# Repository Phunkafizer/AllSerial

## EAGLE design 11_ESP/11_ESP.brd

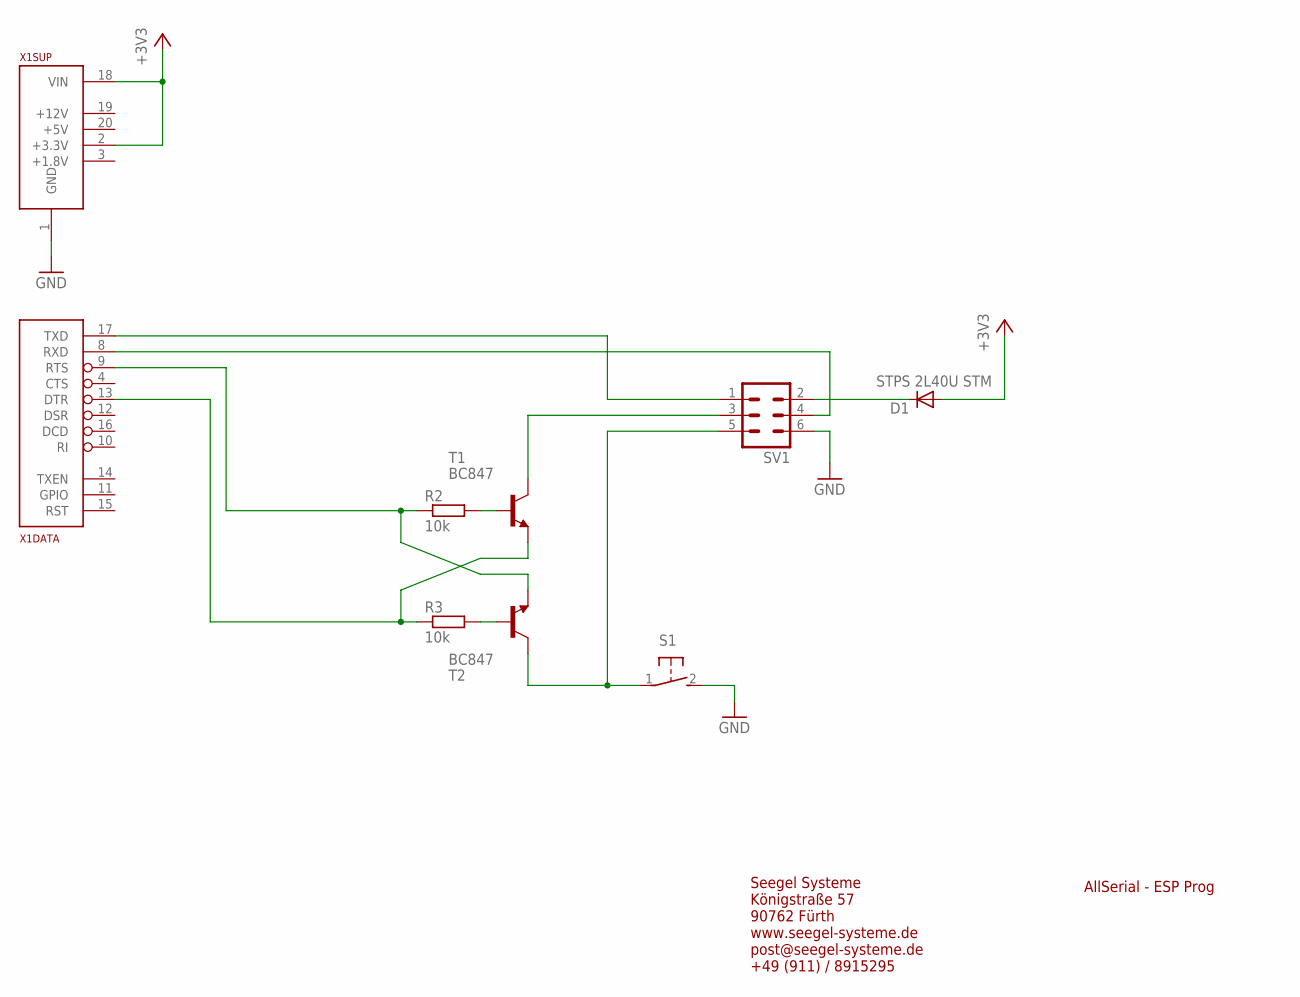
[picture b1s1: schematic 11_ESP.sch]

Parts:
D1: STPS 2L40U STM; DO214AA
R2, R3: 10k; R0805
S1: 31-XX; B3F-31XX
SV1: ML6L
T1, T2: BC847; SOT23
X1: ALLSERIALSLAVE; DAUGHTER-THT

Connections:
+3V3: D1.A, X1.2 (+3.3V), X1.18 (VIN)
GND: S1.2 (S), SV1.6, X1.1 (GND)
unnamed: D1.C, SV1.2
unnamed: R3.1, T1.2 (E), X1.13 (DTR)
unnamed: SV1.3, T1.3 (C)
unnamed: S1.1, SV1.5, T2.3 (C)
unnamed: R2.1, T2.2 (E), X1.9 (RTS)
unnamed: SV1.1, X1.17 (TXD)
unnamed: R2.2, T1.1 (B)
unnamed: R3.2, T2.1 (B)
unnamed: SV1.4, X1.8 (RXD)

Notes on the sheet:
AllSerial - ESP Prog
Seegel Systeme Königstraße 57 90762 Fürth www.seegel-systeme.de post@seegel-systeme.de +49 (911) / 8915295

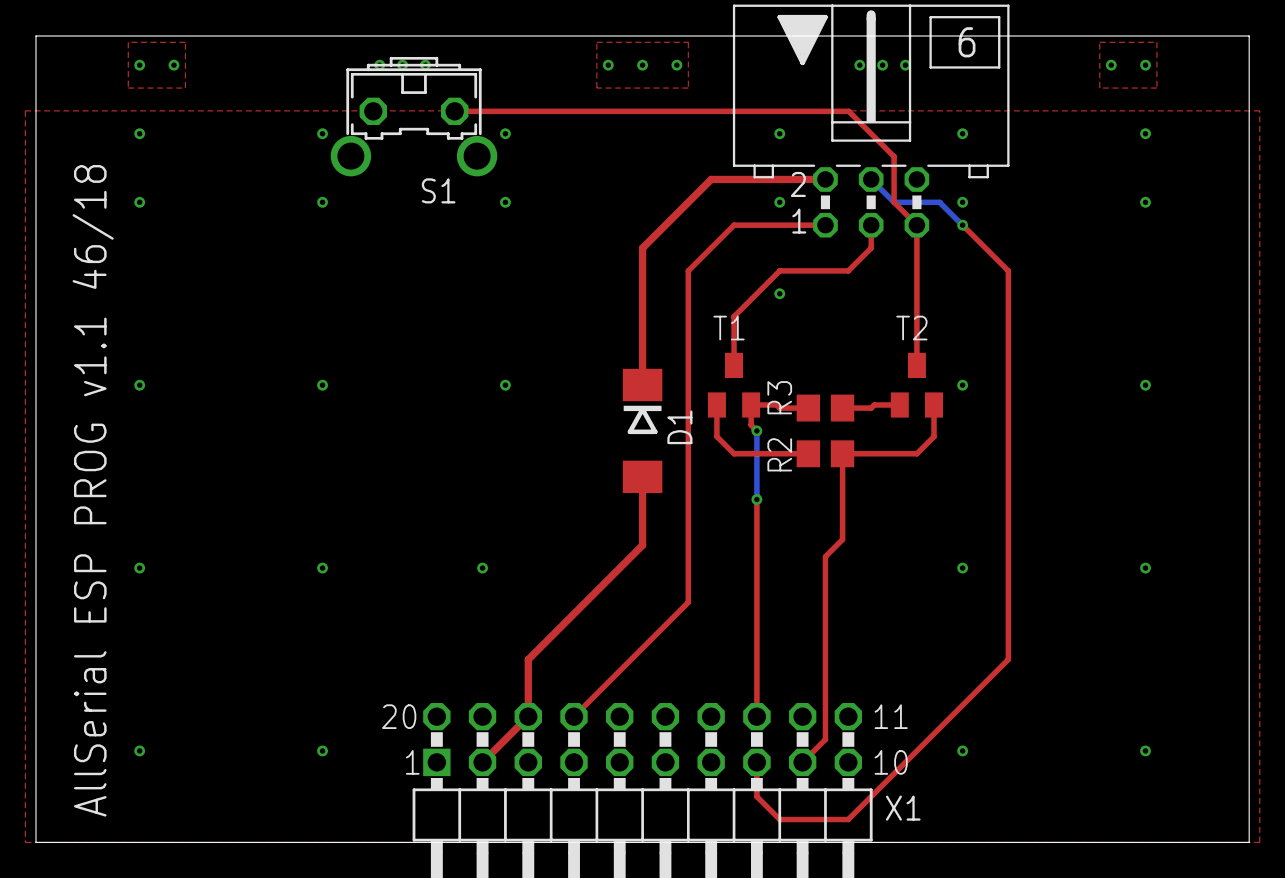
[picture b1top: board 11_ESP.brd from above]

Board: 2 copper layers, 67.4 x 44.8 mm, 8 parts (0 on the bottom side), 11 nets.

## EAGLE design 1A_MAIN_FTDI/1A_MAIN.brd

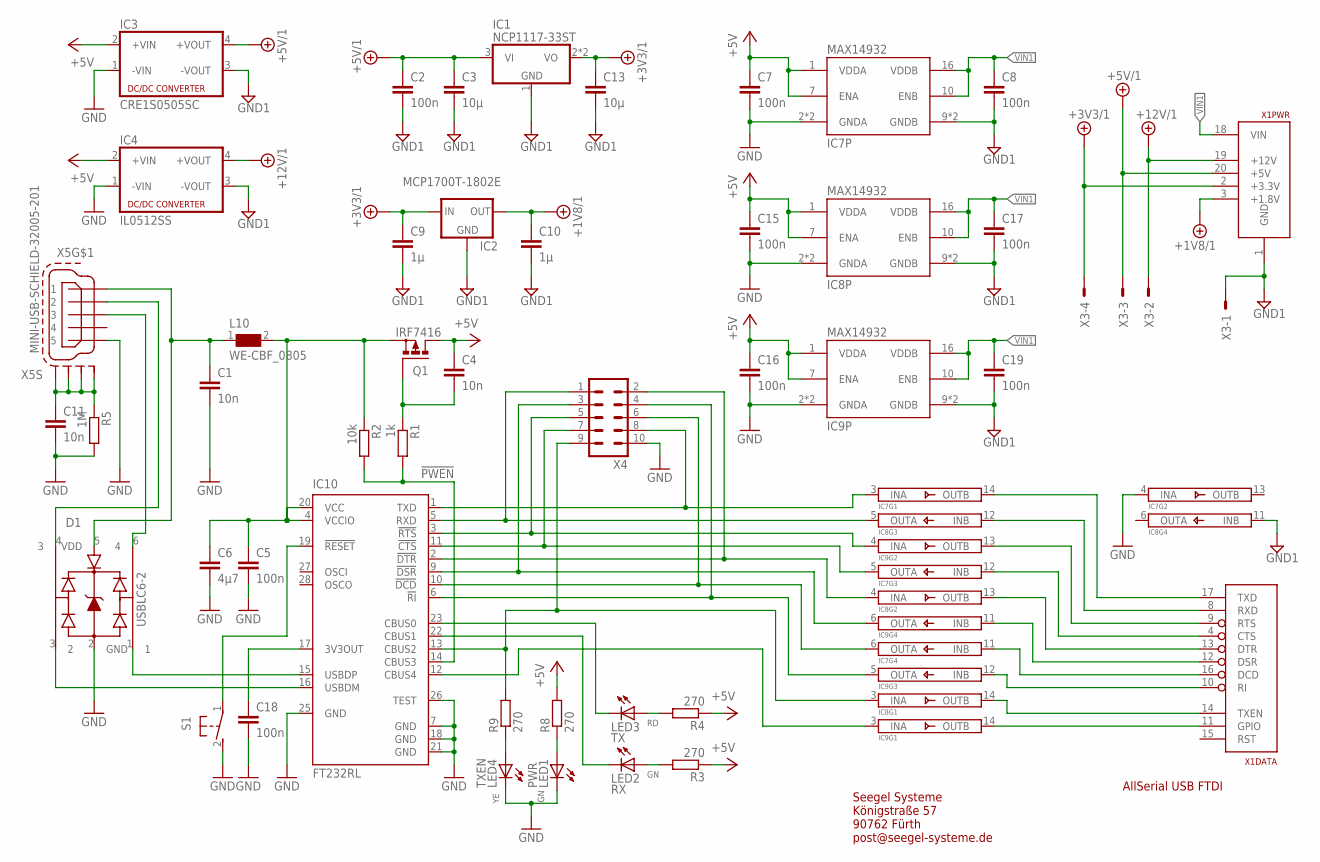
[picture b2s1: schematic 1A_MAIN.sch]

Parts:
C1, C4, C11: 10n; C0805
C2, C5, C7, C8, C15, C16, C17, C18, C19: 100n; C0805
C3, C13: 10µ; C0805
C6: 4µ7; C0805
C9, C10: 1µ; C0805
D1: USBLC6-2; WE-TVS_SOT23-6L
IC1: NCP1117-33ST; SOT223
IC2: MCP1700T-1802E; SOT23
IC3: CRE1S0505SC; MURATA-SC
IC4: IL0512SS; XPPOWER-SIP
IC7, IC8, IC9: MAX14932; SO16
IC10: FT232RL; SSOP28
L10: WE-CBF_0805; 0805
LED1: PWR; CHIPLED_0603
LED2: RX; CHIPLED_0603
LED3: TX; CHIPLED_0603
LED4: TXEN; CHIPLED_0603
Q1: IRF7416; SO-08
R1: 1k; R0805
R2: 10k; R0805
R3, R4, R8, R9: 270; R0805
R5: 1M; R0805
S1: 31-XX; B3F-31XX
X1: ALLSERIALMASTERMM; MAIN-THT
X3: AKL18X-04W; AKL182-04
X4: ML10
X5: MINI-USB-SCHIELD-32005-201; 32005-201

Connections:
!PWEN: IC10.14 (CBUS3), R1.2, R2.2
+1V8/1: C10.1, IC2.2 (OUT), X1.3 (+1.8V)
+3V3/1: C9.1, C13.1, IC1.2 (VO), IC1.4 (VO), IC2.3 (IN), X1.2 (+3.3V), X3.P$4
+5V: C4.1, C7.1, C15.1, C16.1, IC3.2 (+VIN), IC4.2 (+VIN), IC7.1 (VDDA), IC7.7 (ENA), IC8.1 (VDDA), IC8.7 (ENA), IC9.1 (VDDA), IC9.7 (ENA), Q1.5 (D), Q1.6 (D), Q1.7 (D), Q1.8 (D), R3.1, R4.1, R8.2
+5V/1: C2.1, C3.1, IC1.3 (VI), IC3.4 (+VOUT), X1.20 (+5V), X3.P$3
+12V/1: IC4.4 (+VOUT), X1.19 (+12V), X3.P$2
GND: C1.2, C5.2, C6.2, C7.2, C11.2, C15.2, C16.2, C18.2, D1.2 (GND), IC3.1 (-VIN), IC4.1 (-VIN), IC7.2 (GNDA), IC7.4 (INA), IC7.8 (GNDA), IC8.2 (GNDA), IC8.8 (GNDA), IC9.2 (GNDA), IC9.8 (GNDA), IC10.7 (GND), IC10.18 (GND), IC10.21 (GND), IC10.25 (GND), IC10.26 (TEST), LED1.C, LED4.C, R5.2, S1.2 (S), X4.10, X5.5
GND1: C2.2, C3.2, C8.2, C9.2, C10.2, C13.2, C17.2, C19.2, IC1.1 (GND), IC2.1 (GND), IC3.3 (-VOUT), IC4.3 (-VOUT), IC7.9 (GNDB), IC7.15 (GNDB), IC8.9 (GNDB), IC8.11 (INB), IC8.15 (GNDB), IC9.9 (GNDB), IC9.15 (GNDB), X1.1 (GND), X3.P$1
unnamed: IC8.5 (OUTA), IC10.5 (RXD), X4.1
unnamed: IC9.6 (OUTA), IC10.9 (!DSR), X4.3
unnamed: IC8.3 (INA), IC10.13 (CBUS2), R9.2, X4.9
unnamed: LED2.A, R3.2
unnamed: IC10.19 (!RESET), S1.1
unnamed: LED3.A, R4.2
unnamed: LED4.A, R9.1
unnamed: LED1.A, R8.1
unnamed: D1.3 (2), IC10.16 (USBDM)
unnamed: D1.1, IC10.15 (USBDP)
unnamed: C1.1, D1.5 (VDD), L10.1, X5.1
unnamed: D1.4 (3), X5.2
unnamed: IC9.3 (INA), IC10.12 (CBUS4)
unnamed: IC7.3 (INA), IC10.1 (TXD), X4.8
unnamed: D1.6 (4), X5.3
unnamed: C11.1, R5.1, X5.M1 (S1), X5.M2 (S2), X5.M3 (S3), X5.M4 (S4)
unnamed: C18.1, IC10.17 (3V3OUT)
unnamed: IC9.4 (INA), IC10.3 (!RTS), X4.5
unnamed: IC7.5 (OUTA), IC10.11 (!CTS), X4.7
unnamed: IC8.4 (INA), IC10.2 (!DTR), X4.2
unnamed: IC7.6 (OUTA), IC10.10 (!DCD), X4.6
unnamed: IC9.5 (OUTA), IC10.6 (!RI), X4.4
unnamed: C5.1, C6.1, IC10.4 (VCCIO), IC10.20 (VCC), L10.2, Q1.1 (S), Q1.2 (S), Q1.3 (S), R2.1
unnamed: C4.2, Q1.4 (G), R1.1
unnamed: IC7.14 (OUTB), X1.17 (TXD)
unnamed: IC8.12 (INB), X1.8 (RXD)
unnamed: IC9.13 (OUTB), X1.9 (RTS)
unnamed: IC7.12 (INB), X1.4 (CTS)
unnamed: IC8.13 (OUTB), X1.13 (DTR)
unnamed: IC9.11 (INB), X1.12 (DSR)
unnamed: IC7.11 (INB), X1.16 (DCD)
unnamed: IC9.12 (INB), X1.10 (RI)
unnamed: IC8.14 (OUTB), X1.14 (TXEN)
unnamed: IC9.14 (OUTB), X1.11 (GPIO)
RXLED: IC10.22 (CBUS1), LED2.C
TXLED: IC10.23 (CBUS0), LED3.C
VIN1: C8.1, C17.1, C19.1, IC7.10 (ENB), IC7.16 (VDDB), IC8.10 (ENB), IC8.16 (VDDB), IC9.10 (ENB), IC9.16 (VDDB), X1.18 (VIN)

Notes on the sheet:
AllSerial USB FTDI
Seegel Systeme Königstraße 57 90762 Fürth post@seegel-systeme.de

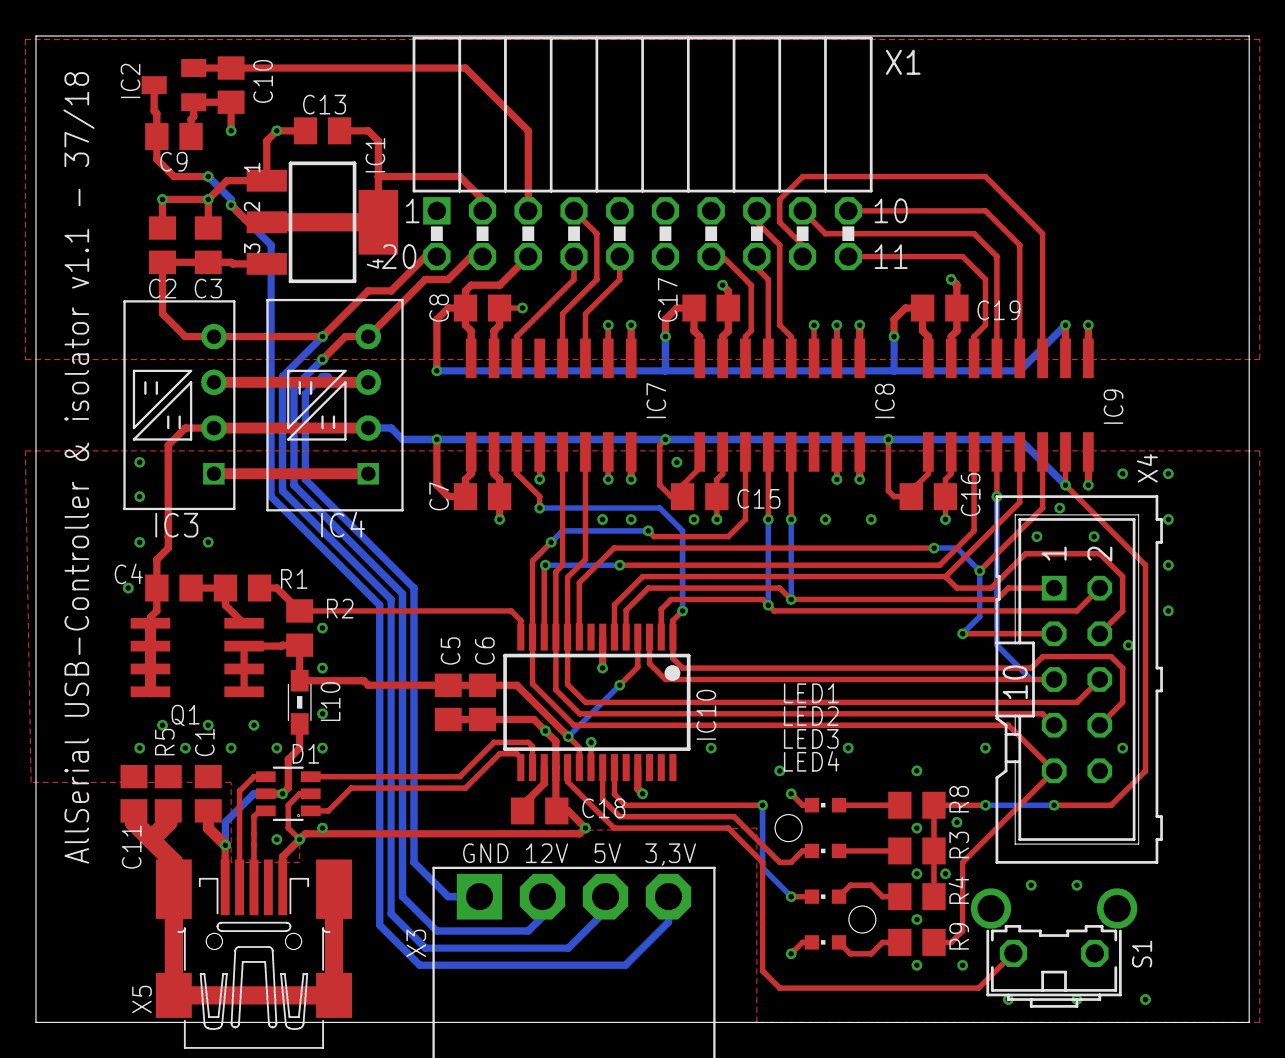
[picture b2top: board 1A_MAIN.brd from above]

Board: 2 copper layers, 67.4 x 54.8 mm, 45 parts (0 on the bottom side), 45 nets.

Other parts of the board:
U$3: 1296.1004

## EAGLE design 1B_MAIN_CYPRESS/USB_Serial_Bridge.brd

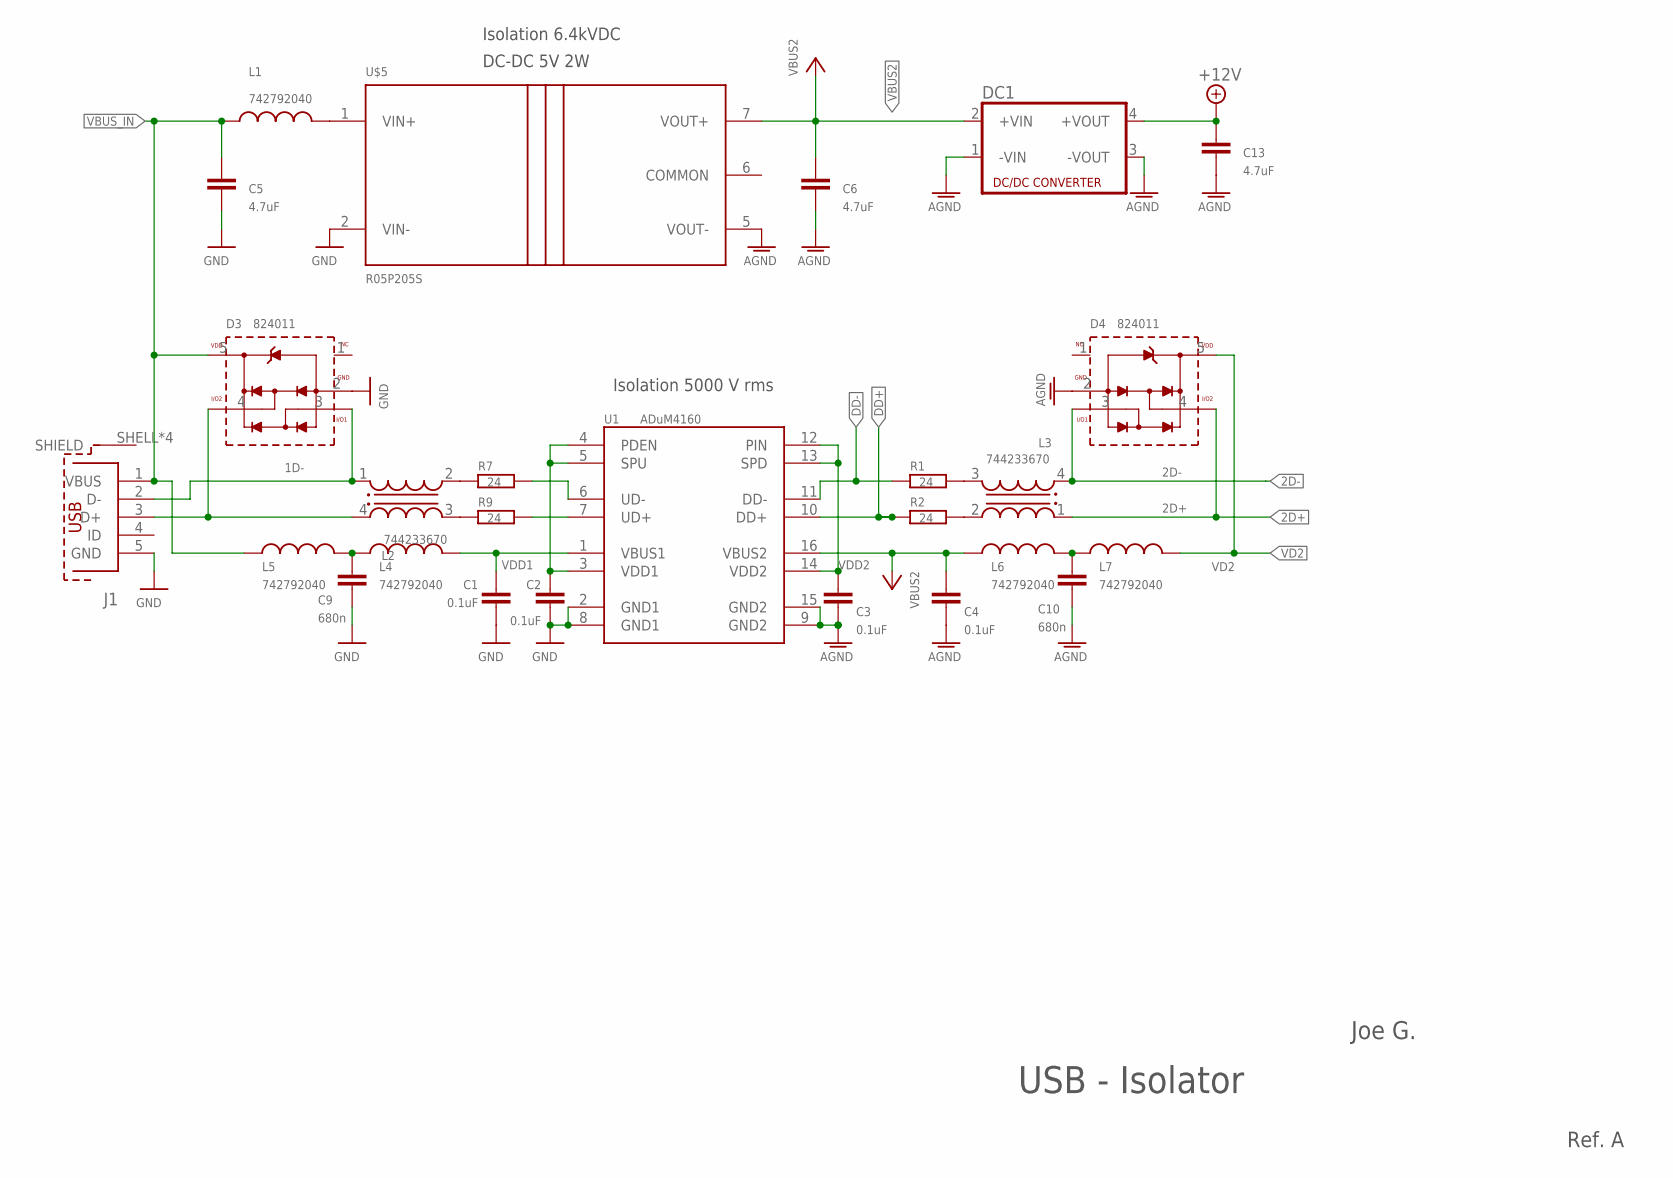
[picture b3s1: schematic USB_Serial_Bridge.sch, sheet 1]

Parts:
C1, C2, C3, C4: 0.1uF; 0805
C5, C6, C13: 4.7uF; 1206
C9: 680n; C0805K
C10: 680n; C0805
D3, D4: 824011; WE-TVS_SOT23-5L
DC1: DC-DC-CONVERTER_NME
J1: 651305142821
L1, L4, L5, L6, L7: 742792040; WE-CBF_0805(W=3.0)
L2, L3: 744233670; WE-CNSW_0805
R1, R2, R7, R9: 24; R0805
U1: ADuM4160; SO16W
U$5: R05P205S; SIP7_RECON

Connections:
1D+: D3.4 (I/O2), J1.3 (D+), L2.4 (1)
1D-: D3.3 (I/O1), J1.2 (D-), L2.1 (4)
2D+: D4.4 (I/O2), L3.1 (4); also elsewhere on the board
2D-: D4.3 (I/O1), L3.4 (1); also elsewhere on the board
+12V: C13.1, DC1.4 (+VOUT); also elsewhere on the board
AGND: C3.2, C4.2, C6.2, C10.2, C13.2, D4.2 (GND), DC1.1 (-VIN), DC1.3 (-VOUT), U1.9 (GND2), U1.15 (GND2), U$5.5 (VOUT-); also elsewhere on the board
COMMON: U$5.6 (COMMON)
DD+: R2.1, U1.10 (DD+); also elsewhere on the board
DD-: R1.1, U1.11 (DD-); also elsewhere on the board
GND: C1.2, C2.2, C5.2, C9.2, D3.2 (GND), J1.5 (GND), U1.2 (GND1), U1.8 (GND1), U$5.2 (VIN-)
unnamed: L2.2 (3), R7.1
unnamed: L3.3 (2), R1.2
unnamed: L3.2 (3), R2.2
unnamed: R9.2, U1.7 (UD+)
unnamed: L2.3 (2), R9.1
unnamed: R7.2, U1.6 (UD-)
unnamed: C9.1, L4.1, L5.2
unnamed: L1.2, U$5.1 (VIN+)
unnamed: C10.1, L6.2, L7.1
VBUS1: C1.1, L4.2, U1.1 (VBUS1)
VBUS2: C4.1, C6.1, DC1.2 (+VIN), L6.1, U1.16 (VBUS2), U$5.7 (VOUT+); also elsewhere on the board
VBUS_IN: C5.1, D3.5 (VDD), J1.1 (VBUS), L1.1, L5.1
VD2: D4.5 (VDD), L7.2; also elsewhere on the board
VDD1: C2.1, U1.3 (VDD1), U1.4 (PDEN), U1.5 (SPU)
VDD2: C3.1, U1.12 (PIN), U1.13 (SPD), U1.14 (VDD2)

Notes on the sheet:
DC-DC 5V 2W
Isolation 5000 V rms
Isolation 6.4kVDC
USB - Isolator
Joe G.
Ref. A

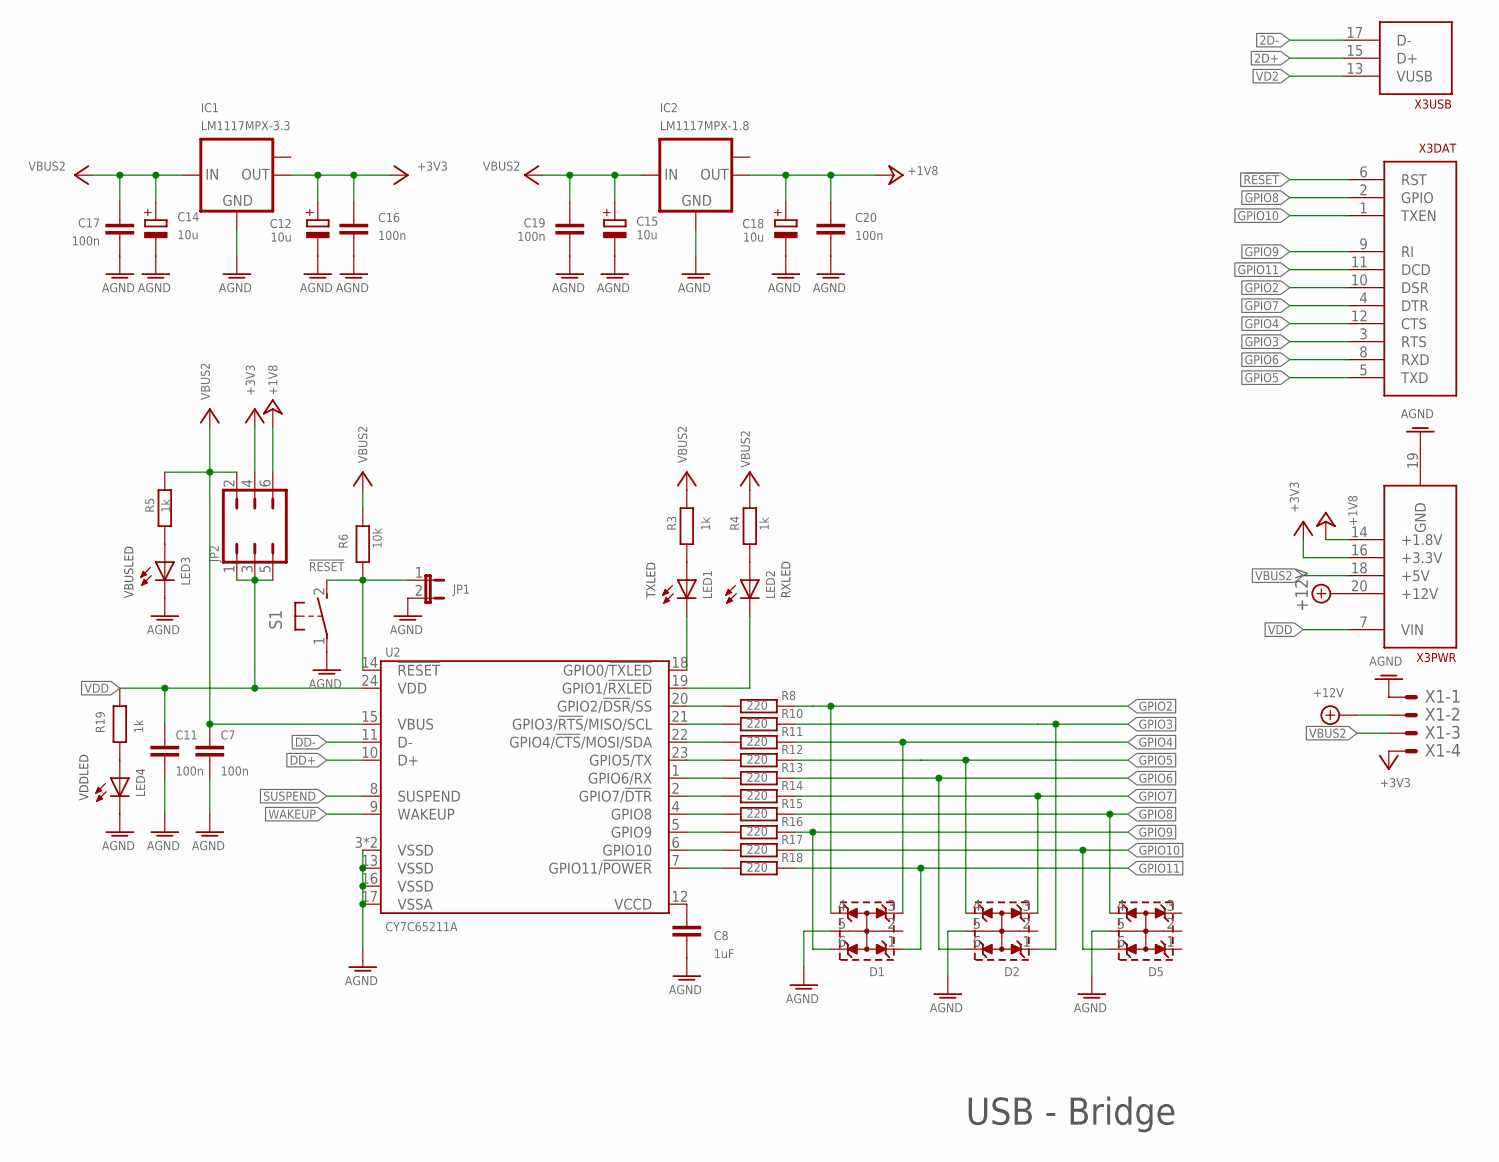
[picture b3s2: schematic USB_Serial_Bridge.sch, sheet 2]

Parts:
C7, C11, C16, C17, C19, C20: 100n; C0805
C8: 1uF; 1206
C12, C14, C15, C18: 10u; SMC_B
D1, D2, D5: WE-TVS_82402304; WE-TVS_SOT23-6L
IC1: LM1117MPX-3.3; SOT223
IC2: LM1117MPX-1.8; SOT223
JP1: JP1E; JP1
JP2: JP3Q
LED1, LED2, LED3, LED4: LEDSML0603; SML0603
R3, R4, R5, R19: 1k; M0805
R6: 10k; M0805
R8, R10, R11, R12, R13, R14, R15, R16, R17, R18: 220; M0805
S1: SWITCH-OMRON_31-XX; SWITCH-OMRON_B3F-31XX
U2: CY7C65211A; QFN-24
X1: AKL18X-04W; AKL182-04
X3: ALLSERIALMM; MAIN-THT

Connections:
2D+: X3.15 (D+); also elsewhere on the board
2D-: X3.17 (D-); also elsewhere on the board
!RESET: JP1.1, R6.1, S1.2 (S), U2.14 (!RESET), X3.6 (RST)
+1V8: C18.+, C20.1, IC2.2 (OUT), JP2.6, X3.14 (+1.8V)
+3V3: C12.+, C16.1, IC1.2 (OUT), JP2.4, X1.P$4, X3.16 (+3.3V)
+12V: X1.P$2, X3.20 (+12V); also elsewhere on the board
AGND: C7.2, C8.2, C11.2, C12.-, C14.-, C15.-, C16.2, C17.2, C18.-, C19.2, C20.2, D1.5 (GND), D2.5 (GND), D5.5 (GND), IC1.1 (GND), IC2.1 (GND), JP1.2, LED3.C, LED4.C, S1.1, U2.3 (VSSD), U2.13 (VSSD), U2.16 (VSSD), U2.17 (VSSA), U2.EP (VSSD), X1.P$1, X3.19 (GND); also elsewhere on the board
DD+: U2.10 (D+); also elsewhere on the board
DD-: U2.11 (D-); also elsewhere on the board
GPIO2: D1.4 (3), R8.1, X3.10 (DSR)
GPIO3: D2.1, R10.1, X3.3 (RTS)
GPIO4: D1.3 (2), R11.1, X3.12 (CTS)
GPIO5: D2.4 (3), R12.1, X3.5 (TXD)
GPIO6: D2.6 (4), R13.1, X3.8 (RXD)
GPIO7: D2.3 (2), R14.1, X3.4 (DTR)
GPIO8: D5.4 (3), R15.1, X3.2 (GPIO)
GPIO9: D1.6 (4), R16.1, X3.9 (RI)
GPIO10: D5.6 (4), R17.1, X3.1 (TXEN)
GPIO11: D1.1, R18.1, X3.11 (DCD)
unnamed: C8.1, U2.12 (VCCD)
unnamed: LED4.A, R19.1
unnamed: LED1.A, R3.1
unnamed: LED2.A, R4.1
unnamed: LED1.C, U2.18 (GPIO0/!TXLED)
unnamed: LED2.C, U2.19 (GPIO1/!RXLED)
unnamed: R8.2, U2.20 (GPIO2/!DSR!/SS)
unnamed: R10.2, U2.21 (GPIO3/!RTS!/MISO/SCL)
unnamed: LED3.A, R5.1
unnamed: R11.2, U2.22 (GPIO4/!CTS!/MOSI/SDA)
unnamed: R12.2, U2.23 (GPIO5/TX)
unnamed: R13.2, U2.1 (GPIO6/RX)
unnamed: R14.2, U2.2 (GPIO7/!DTR)
unnamed: R15.2, U2.4 (GPIO8)
unnamed: R16.2, U2.5 (GPIO9)
unnamed: R17.2, U2.6 (GPIO10)
unnamed: R18.2, U2.7 (GPIO11/!POWER)
SUSPEND: U2.8 (SUSPEND)
VBUS2: C7.1, C14.+, C15.+, C17.1, C19.1, IC1.3 (IN), IC2.3 (IN), JP2.2, R3.2, R4.2, R5.2, R6.2, U2.15 (VBUS), X1.P$3, X3.18 (+5V); also elsewhere on the board
VD2: X3.13 (VUSB); also elsewhere on the board
VDD: C11.1, JP2.1, JP2.3, JP2.5, R19.2, U2.24 (VDD), X3.7 (VIN)
WAKEUP: U2.9 (WAKEUP)

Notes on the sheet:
TXLED
RXLED
VBUSLED
VDDLED
USB - Bridge

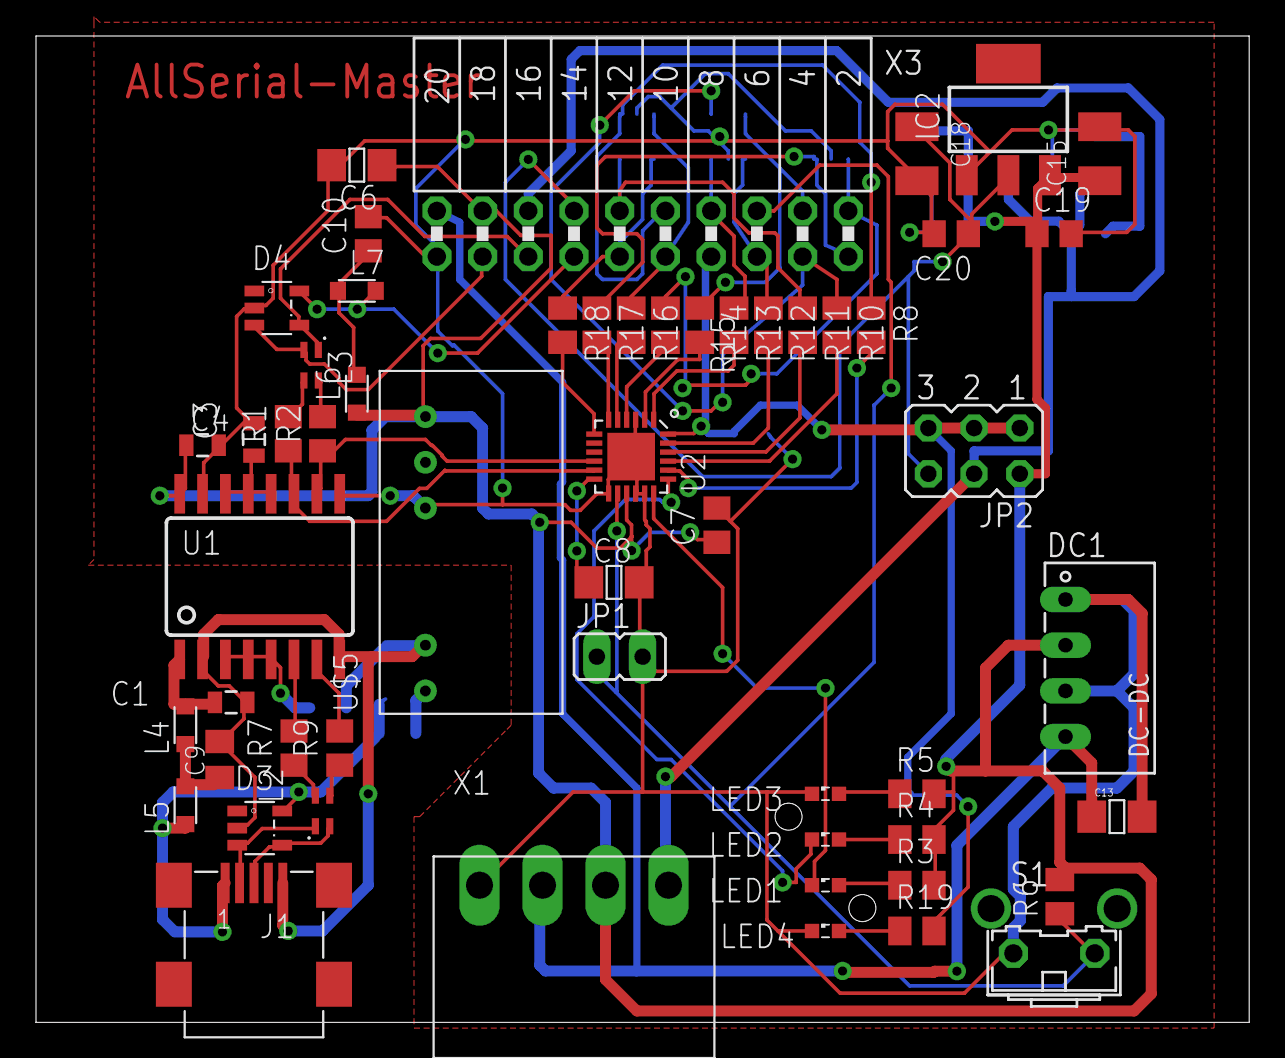
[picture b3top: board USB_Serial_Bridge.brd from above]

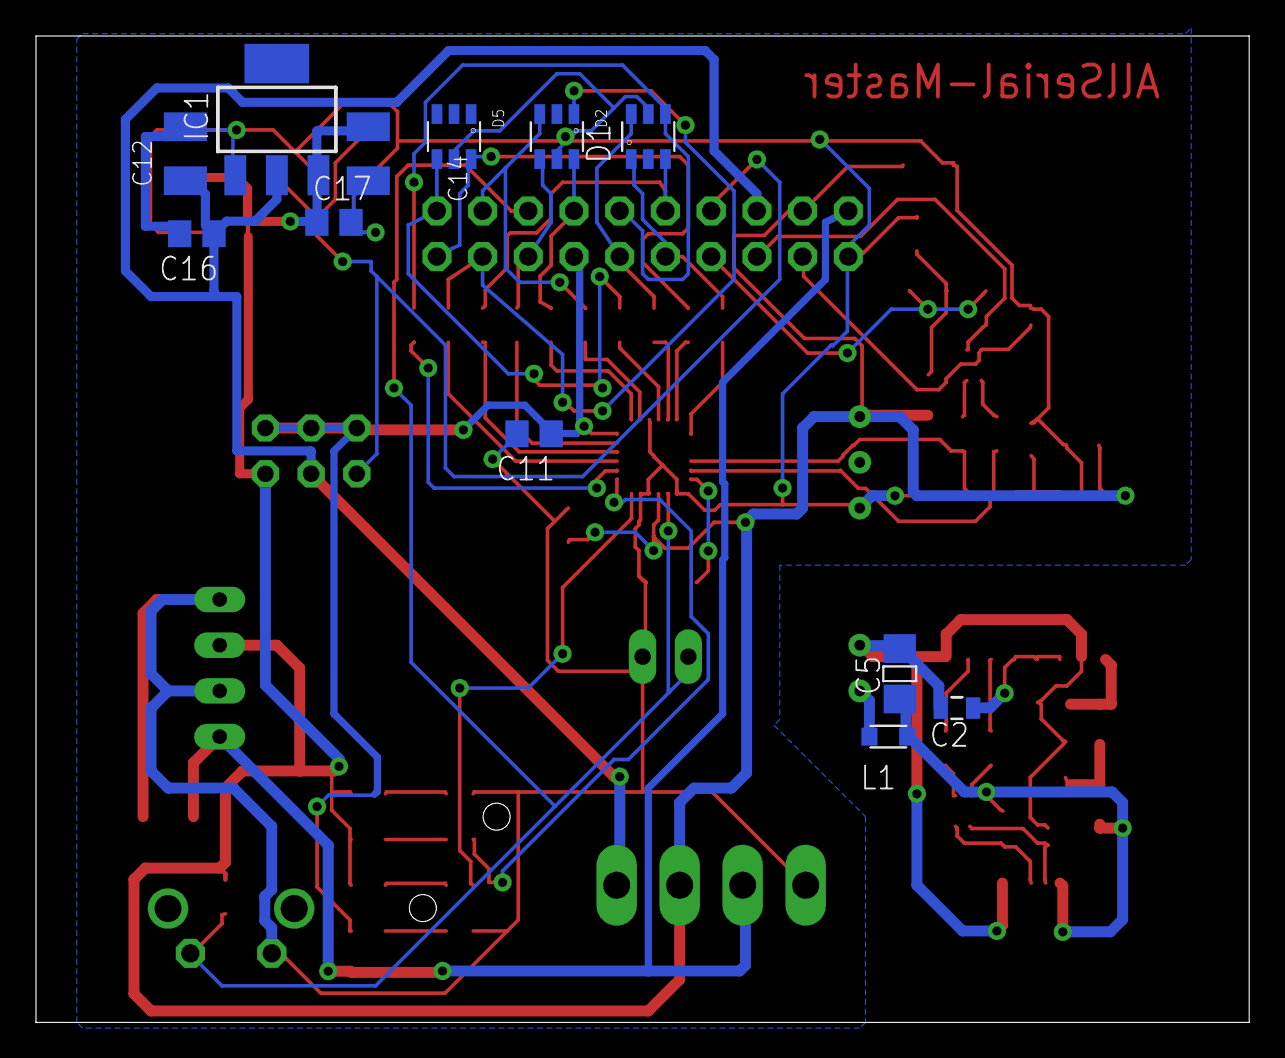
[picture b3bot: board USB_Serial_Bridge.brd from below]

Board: 2 copper layers, 67.4 x 54.8 mm, 68 parts (12 on the bottom side), 55 nets.

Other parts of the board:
U$1: 1296.1004

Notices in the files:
parts and their libraries:
EagleLibrary_Wuerth_Elektronik_eiSos_Ver: Copyright: Würth Elektronik
